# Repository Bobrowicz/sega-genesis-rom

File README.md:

# sega-genesis-rom
sega genesis reproduction rom pcb

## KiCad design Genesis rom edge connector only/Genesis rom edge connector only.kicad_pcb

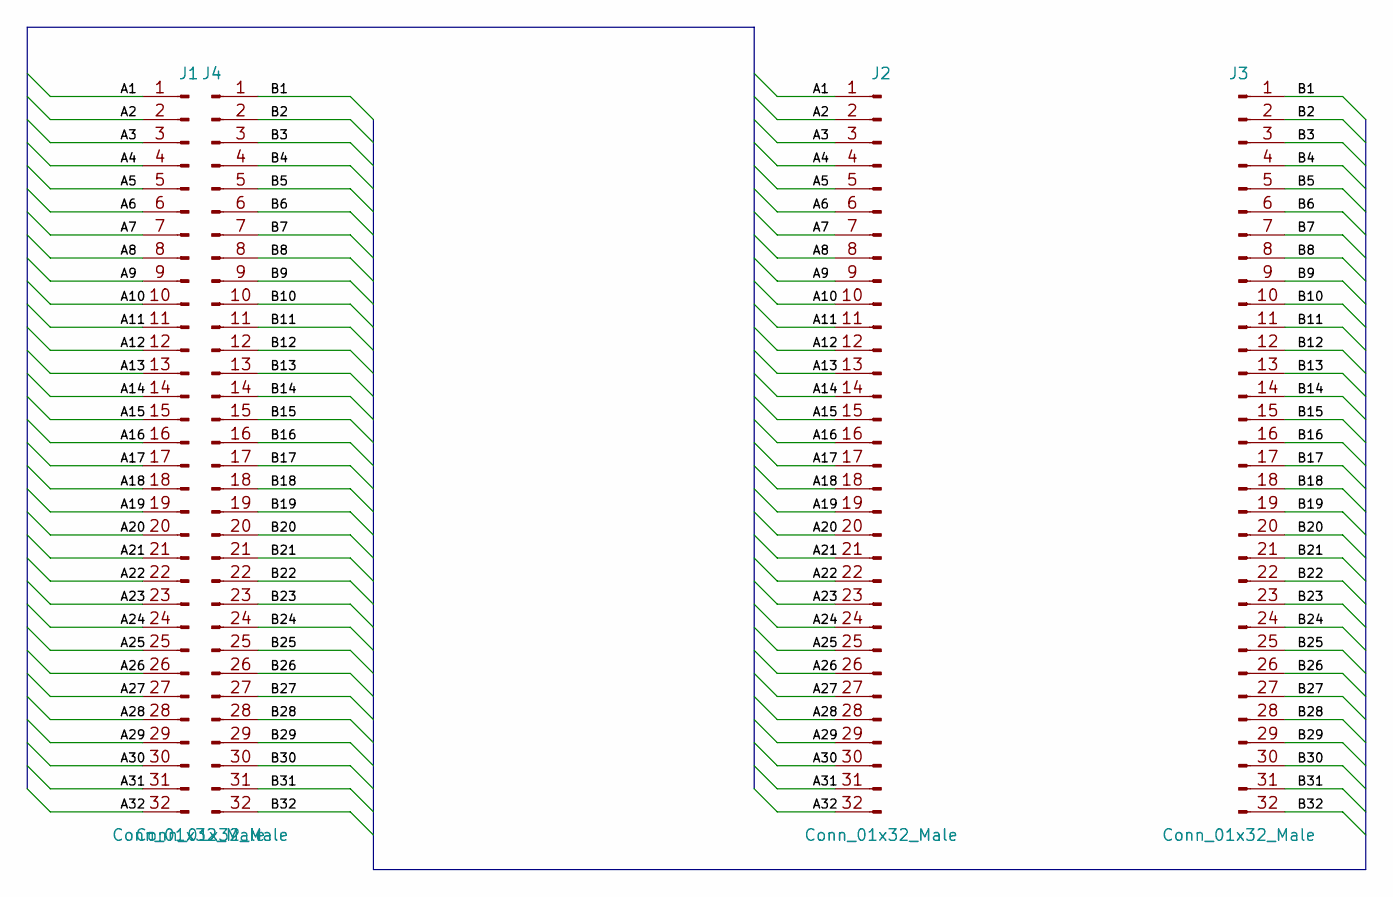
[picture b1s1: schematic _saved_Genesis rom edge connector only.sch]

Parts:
J1, J4: Conn_01x32_Male; Sega_Genesis
J2, J3: Conn_01x32_Male; Pin_Header_Straight_1x32_Pitch2.54mm

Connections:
/A1: J1.1, J2.1
/A2: J1.2, J2.2
/A3: J1.3, J2.3
/A4: J1.4, J2.4
/A5: J1.5, J2.5
/A6: J1.6, J2.6
/A7: J1.7, J2.7
/A8: J1.8, J2.8
/A9: J1.9, J2.9
/A10: J1.10, J2.10
/A11: J1.11, J2.11
/A12: J1.12, J2.12
/A13: J1.13, J2.13
/A14: J1.14, J2.14
/A15: J1.15, J2.15
/A16: J1.16, J2.16
/A17: J1.17, J2.17
/A18: J1.18, J2.18
/A19: J1.19, J2.19
/A20: J1.20, J2.20
/A21: J1.21, J2.21
/A22: J1.22, J2.22
/A23: J1.23, J2.23
/A24: J1.24, J2.24
/A25: J1.25, J2.25
/A26: J1.26, J2.26
/A27: J1.27, J2.27
/A28: J1.28, J2.28
/A29: J1.29, J2.29
/A30: J1.30, J2.30
/A31: J1.31, J2.31
/A32: J1.32, J2.32
/B1: J3.1, J4.1
/B2: J3.2, J4.2
/B3: J3.3, J4.3
/B4: J3.4, J4.4
/B5: J3.5, J4.5
/B6: J3.6, J4.6
/B7: J3.7, J4.7
/B8: J3.8, J4.8
/B9: J3.9, J4.9
/B10: J3.10, J4.10
/B11: J3.11, J4.11
/B12: J3.12, J4.12
/B13: J3.13, J4.13
/B14: J3.14, J4.14
/B15: J3.15, J4.15
/B16: J3.16, J4.16
/B17: J3.17, J4.17
/B18: J3.18, J4.18
/B19: J3.19, J4.19
/B20: J3.20, J4.20
/B21: J3.21, J4.21
/B22: J3.22, J4.22
/B23: J3.23, J4.23
/B24: J3.24, J4.24
/B25: J3.25, J4.25
/B26: J3.26, J4.26
/B27: J3.27, J4.27
/B28: J3.28, J4.28
/B29: J3.29, J4.29
/B30: J3.30, J4.30
/B31: J3.31, J4.31
/B32: J3.32, J4.32

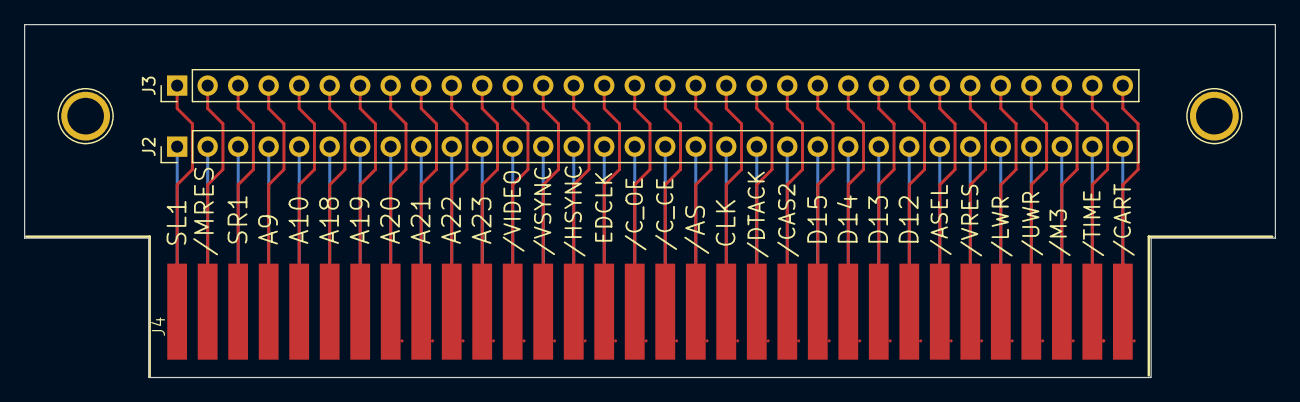
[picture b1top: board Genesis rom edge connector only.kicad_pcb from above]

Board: 2 copper layers, 104.1 x 29.4 mm, 4 parts (1 on the bottom side), 64 nets.

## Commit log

2018-10-04 edge connector adapter created
2018-10-15 started on programmer firmware
    implemented basic functions to read, write and erase SST_39F040
2018-11-03 basic flash functions are working
    Finished implementing basic flash functions: read byte, write byte, erase all, check mem type.
    Fixed silk screen typo on pcb.
2018-11-04 flash programmer wiring
    added fritzing layout of the arduino flash programmer
